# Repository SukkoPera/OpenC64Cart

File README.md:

# OpenC64Cart
OpenC64Cart is an Open Hardware Cartridge for the Commodore 64. It only supports 8 KB ROM images. A variant that supports 16 KB ROMs is [available separately](https://github.com/SukkoPera/OpenC64Cart16K).

### Summary
OpenC64Cart is designed to accept a 64 KB (512 Kilobit) (E)EPROM with a 27512-style pinout:

Such chips can hold up to 8 cartridge images, which can then be selected by jumpers. Other jumpers allow the selection ROM type and of EXROM or GAME mode, achieving compatibility with many different types of ROM, from "simple" games to Ultimax cartridges.
 
The recommended part is Winbond W27C512 (or W27E512, I don't understand what differences they have), which is widely available, cheap and electrically erasable, which avoids the need for a clunky UV-eraser. This is the only part that was thoroughly tested. Other parts, even smaller in size, will probably work, but will require an ad-hoc configuration.
 
Usage is straightforward: just insert the EEPROM in the socket making sure that the notch and all pins are aligned, set the jumpers as desired and plug the cartridge in your C64.
 
### Configuration
**IMPORTANT: ALWAYS TURN YOUR C64 OFF BEFORE MOVING THE CONFIGURATION JUMPERS.**
 
When flashing the contents, make sure that every file is exactly 8192 bytes long and just concatenate them. Then use the following table to set the jumper configuration for your image of choice:

| ROM Image # | A13 | A14 | A15 |
|-------------|-----|-----|-----|
| 1           |  L  |  L  |  L  |
| 2           |  H  |  L  |  L  |
| 3           |  L  |  H  |  L  |
| 4           |  H  |  H  |  L  |
| 5           |  L  |  L  |  H  |
| 6           |  H  |  L  |  H  |
| 7           |  L  |  H  |  H  |
| 8           |  H  |  H  |  H  |
 
You will also need to configure the ROM and EXROM/GAME jumpers for the chosen image, according to the following table:

| Mode        | ROM  | GAME  | EXROM | Notes |
|-------------|------|-------|-------|-------|
| ROML        |  LO  | Open  | Close | Most common setting
| ROMH        |  HI  | Close | Close | Used for 16 KB cartridges, so does not apply here
| Ultimax     |  HI  | Close | Open  | Originally used for cartridges for the Japanese MAX Machine, will work even if the kernal ROM is damaged |
 
Note that with this cartridge GAME and EXROM must NEVER closed at the same time.
 
### License
OpenC64Cart is Open Hardware. If you make any modifications to the board, please contribute them back.

### Support the Project
Since the project is open you are free to get the PCBs made by your preferred manufacturer, however in case you want to support the development, you can order them from PCBWay through this link:

You get cheap, professionally-made and good quality PCBs, I get some credit that will help with this and [other projects](https://www.pcbway.com/project/member/shareproject/?bmbid=41100). You won't even have to worry about the various PCB options, it's all pre-configured for you!

Also, if you still have to register to that site, [you can use this link](https://www.pcbway.com/setinvite.aspx?inviteid=41100) to get some bonus initial credit (and yield me some more).

Again, if you want to use another manufacturer, feel free to, don't feel obligated :).

### Get Support
If you need help or have questions, you can join [the official Telegram group](https://t.me/joinchat/HUHdWBC9J9JnYIrvTYfZmg).
 
### Thanks
The following links were useful during the development of this project:
- https://www.c64-wiki.com/wiki/Expansion_Port
- http://blog.worldofjani.com/?p=879
- https://ist.uwaterloo.ca/~schepers/roms.html
- http://smisioto.no-ip.org/elettronica/kicad/kicad.htm

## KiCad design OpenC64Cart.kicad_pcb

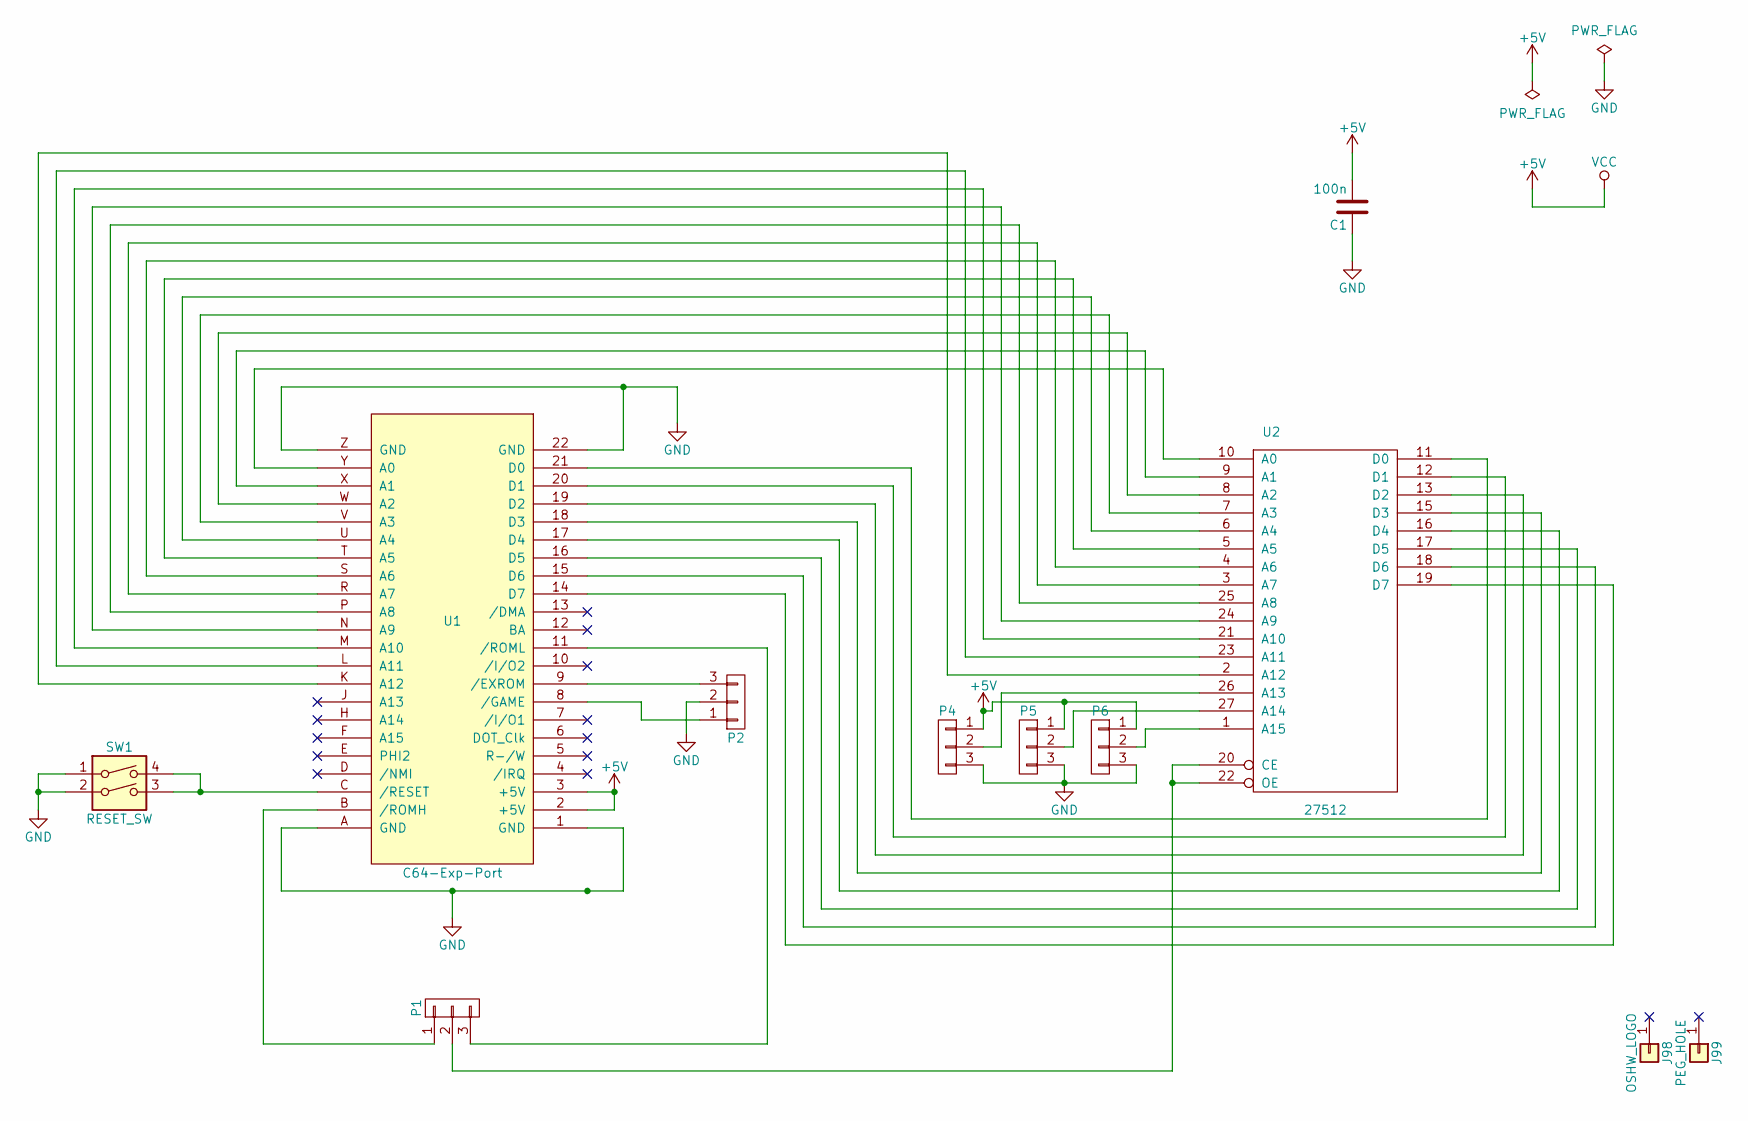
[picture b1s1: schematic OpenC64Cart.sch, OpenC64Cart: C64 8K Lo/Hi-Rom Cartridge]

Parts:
C1: 100n; C_0805+THT
J98: OSHW_LOGO; Logo_copper_OSHW_12x13mm
J99: PEG_HOLE; 1pin
P1, P2, P4, P5, P6: CONN_01X03; Pin_Header_Straight_1x03-NoSilkS
SW1: RESET_SW; PCB_PUSH
U1: C64-Exp-Port; C64-Cart
U2: 27512; dil_28-600_socket

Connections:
+5V: C1.2, P4.1, P5.1, P6.1, U1.2 (+5V), U1.3 (+5V), U2.28 (VCC)
GND: C1.1, P2.2, P4.3, P5.3, P6.3, SW1.1, SW1.2, U1.1 (GND), U1.22 (GND), U1.A (GND), U1.Z (GND), U2.14 (GND)
unnamed: P1.1, U1.B (/ROMH)
unnamed: P1.2, U2.20 (CE), U2.22 (OE)
unnamed: P1.3, U1.11 (/ROML)
unnamed: P2.1, U1.8 (/GAME)
unnamed: P2.3, U1.9 (/EXROM)
unnamed: P4.2, U2.26 (A13)
unnamed: P5.2, U2.27 (A14)
unnamed: P6.2, U2.1 (A15)
unnamed: SW1.3, SW1.4, U1.C (/RESET)
unnamed: U1.14 (D7), U2.19 (D7)
unnamed: U1.15 (D6), U2.18 (D6)
unnamed: U1.16 (D5), U2.17 (D5)
unnamed: U1.17 (D4), U2.16 (D4)
unnamed: U1.18 (D3), U2.15 (D3)
unnamed: U1.19 (D2), U2.13 (D2)
unnamed: U1.20 (D1), U2.12 (D1)
unnamed: U1.21 (D0), U2.11 (D0)
unnamed: U1.K (A12), U2.2 (A12)
unnamed: U1.L (A11), U2.23 (A11)
unnamed: U1.M (A10), U2.21 (A10)
unnamed: U1.N (A9), U2.24 (A9)
unnamed: U1.P (A8), U2.25 (A8)
unnamed: U1.R (A7), U2.3 (A7)
unnamed: U1.S (A6), U2.4 (A6)
unnamed: U1.T (A5), U2.5 (A5)
unnamed: U1.U (A4), U2.6 (A4)
unnamed: U1.V (A3), U2.7 (A3)
unnamed: U1.W (A2), U2.8 (A2)
unnamed: U1.X (A1), U2.9 (A1)
unnamed: U1.Y (A0), U2.10 (A0)

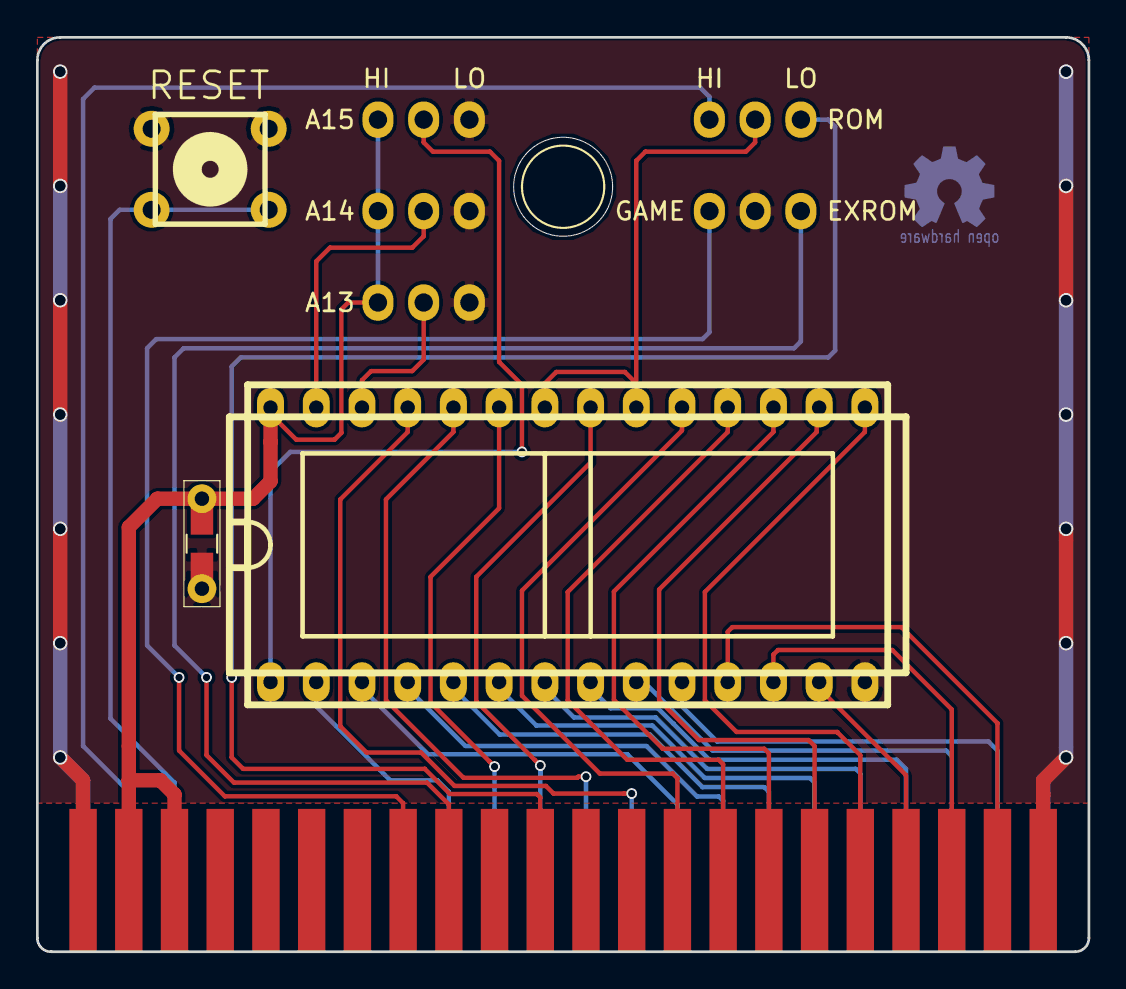
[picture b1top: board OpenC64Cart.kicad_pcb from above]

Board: 2 copper layers, 58.4 x 50.8 mm, 11 parts (1 on the bottom side), 32 nets.

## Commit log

2017-09-28 Routing adjustments
2017-09-28 Add peg hole, smooth corners and routing adjustments
2017-10-04 Add schematic and renders
2017-10-04 Fix 3D models
2017-10-04 Fix descriptor
2017-10-04 Initial work on README
2017-12-15 Add .gitignore
2017-12-30 Use SMD/THT combo footprint for cap, make peg hole 0.5mm bigger, fix parts for latest Kicad Thanks bigby for the peg hole size hint!
2018-01-04 Final touches for V2
2018-01-04 More final touches
2018-01-04 Crop images
2018-01-08 Use a single jumper for GAME/EXROM
2018-01-08 Update images
2018-01-08 Update schematics
2018-01-14 Minor adjustments. Update images.
